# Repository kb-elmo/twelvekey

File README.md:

# Twelvekey

[![CC BY-NC-SA 4.0][cc-by-nc-sa-shield]][cc-by-nc-sa]

### Simple 12-key mechanical macropad

---

[STEP files for the case](case/)

[KiCAD PCB files](pcb/)

[Gerbers for PCB production](pcb/fab/twelvekey.zip)

[JLCPCB BOM](pcb/fab/twelvekey_bom_jlc.csv)

[JLCPCB CPL](pcb/fab/twelvekey_cpl_jlc.csv)

[Vial-QMK firmware](firmware/vial-qmk)

---

---

This work is licensed under a
[Creative Commons Attribution-NonCommercial-ShareAlike 4.0 International License][cc-by-nc-sa].

[![CC BY-NC-SA 4.0][cc-by-nc-sa-image]][cc-by-nc-sa]

[cc-by-nc-sa]: http://creativecommons.org/licenses/by-nc-sa/4.0/
[cc-by-nc-sa-image]: https://licensebuttons.net/l/by-nc-sa/4.0/88x31.png
[cc-by-nc-sa-shield]: https://img.shields.io/badge/License-CC%20BY--NC--SA%204.0-lightgrey.svg

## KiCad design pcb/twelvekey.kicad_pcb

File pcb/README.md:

# Twelvekey PCB

### Features

- In-switch LEDs
- Powered by an Atmega328p
- Basic ESD and overvoltage protection
- Centered USB type-C port for a detachable cable
- Fully programmable using [QMK](https://qmk.fm) and [Vial](https://get.vial.today)

---

### Preview

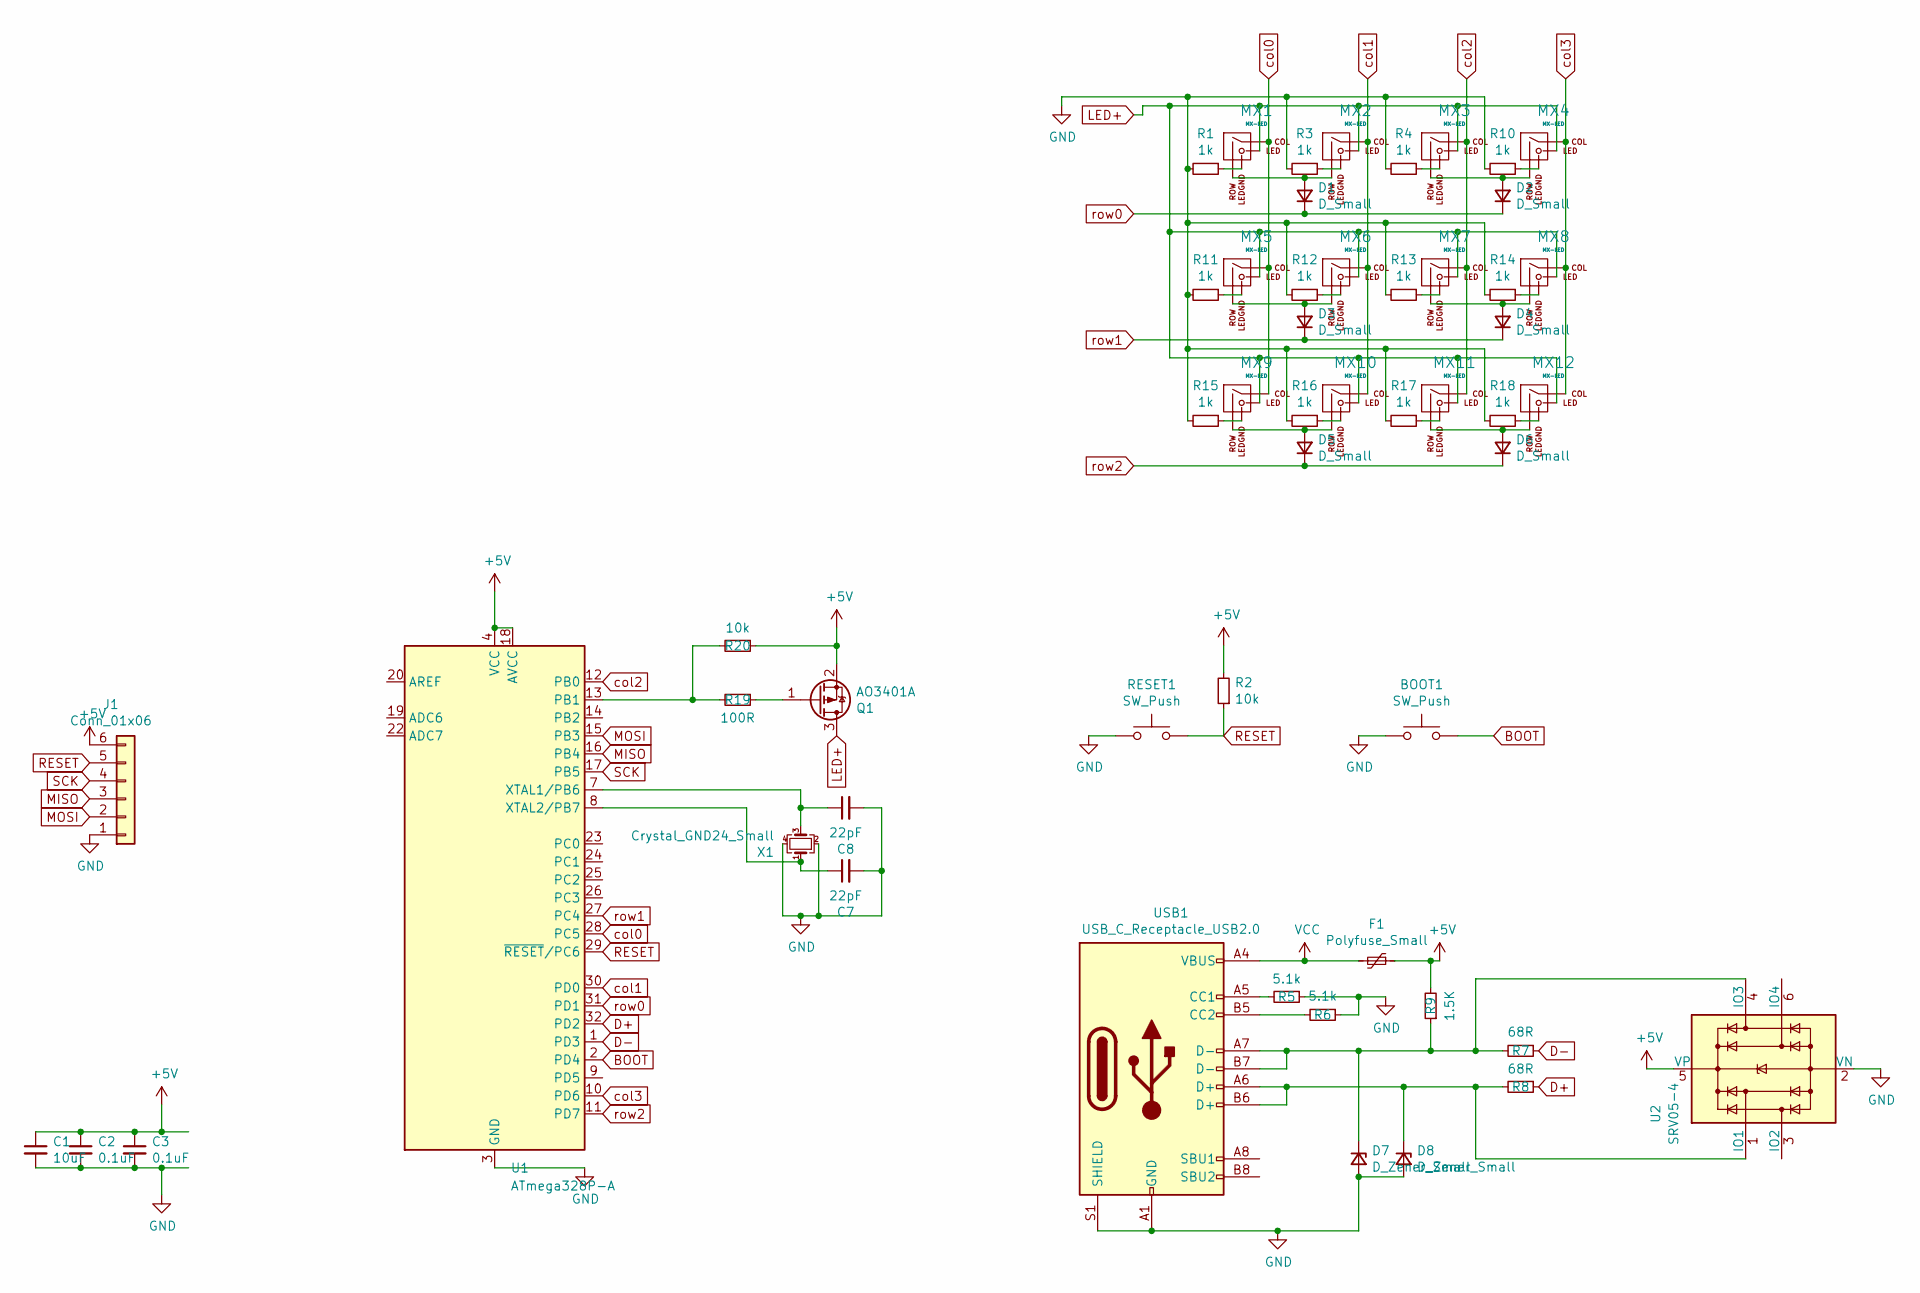
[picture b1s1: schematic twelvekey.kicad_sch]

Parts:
BOOT1: SW_Push; SKQG-1155865; LCSC C2762971
C1: 10uF; C_0805_2012Metric; LCSC C1713
C2, C3: 0.1uF; C_0805_2012Metric; LCSC C38141
C7, C8: 22pF; C_0805_2012Metric; LCSC C24658
D1, D2, D3, D4, D5, D6: D_Small; D_SOT-23_ANK; LCSC C408391
D7, D8: D_Zener_Small; D_SOD-123; LCSC C173412
F1: Polyfuse_Small; Fuse_1206_3216Metric; LCSC C151133
J1: Conn_01x06; PinHeader_1x06_P1.27mm_Vertical
MX1, MX2, MX3, MX4, MX5, MX6, MX7, MX8, MX9, MX10, MX11, MX12: MX-LED; MXOnly-1U
Q1: AO3401A; SOT-23; LCSC C15127
R1, R3, R4, R10, R11, R12, R13, R14, R15, R16, R17, R18: 1k; R_0805_2012Metric; LCSC C17513
R2, R20: 10k; R_0805_2012Metric; LCSC C17414
R5, R6: 5.1k; R_0805_2012Metric; LCSC C27834
R7, R8: 68R; R_0805_2012Metric; LCSC C17802
R9: 1.5K; R_0805_2012Metric; LCSC C4310
R19: 100R; R_0805_2012Metric; LCSC C17408
RESET1: SW_Push; SKQG-1155865; LCSC C2762971
U1: ATmega328P-A; TQFP-32_7x7mm_P0.8mm; LCSC C14877
U2: SRV05-4; SOT-23-6; LCSC C558418
USB1: USB_C_Receptacle_USB2.0; USB_C_Receptacle_HRO_TYPE-C-31-M-12; LCSC C165948
X1: Crystal_GND24_Small; Crystal_SMD_3225-4Pin_3.2x2.5mm; LCSC C13738

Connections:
+5V: C1.1, C2.1, C3.1, F1.1, J1.6, Q1.2 (S), R2.2, R9.2, R20.1, U1.4 (VCC), U1.6 (VCC), U1.18 (AVCC), U2.5 (VP)
BOOT: BOOT1.2, U1.2 (PD4); also elsewhere on the board
D+: R8.1, U1.32 (PD2)
D-: R7.1, U1.1 (PD3)
GND: BOOT1.1, C1.2, C2.2, C3.2, C7.2, C8.2, D7.2 (A), D8.2 (A), J1.1, R1.2, R3.2, R4.2, R5.1, R6.1, R10.2, R11.2, R12.2, R13.2, R14.2, R15.2, R16.2, R17.2, R18.2, RESET1.1, U1.3 (GND), U1.5 (GND), U1.21 (GND), U2.2 (VN), USB1.A1 (GND), USB1.A12 (GND), USB1.B1 (GND), USB1.B12 (GND), USB1.S1 (SHIELD), X1.2, X1.4; also elsewhere on the board
LED+: MX1.3 (LED), MX2.3 (LED), MX3.3 (LED), MX4.3 (LED), MX5.3 (LED), MX6.3 (LED), MX7.3 (LED), MX8.3 (LED), MX9.3 (LED), MX10.3 (LED), MX11.3 (LED), MX12.3 (LED), Q1.3 (D)
MISO: J1.3, U1.16 (PB4)
MOSI: J1.2, U1.15 (PB3)
unnamed: D1.2 (A), MX1.2 (ROW), MX2.2 (ROW)
unnamed: D2.2 (A), MX3.2 (ROW), MX4.2 (ROW)
unnamed: D3.2 (A), MX5.2 (ROW), MX6.2 (ROW)
unnamed: D4.2 (A), MX7.2 (ROW), MX8.2 (ROW)
unnamed: D5.2 (A), MX9.2 (ROW), MX10.2 (ROW)
unnamed: D6.2 (A), MX11.2 (ROW), MX12.2 (ROW)
unnamed: D7.1 (K), R7.2, R9.1, U2.4 (IO3), USB1.A7 (D-), USB1.B7 (D-)
unnamed: D8.1 (K), R8.2, U2.1 (IO1), USB1.A6 (D+), USB1.B6 (D+)
unnamed: MX1.4 (LEDGND), R1.1
unnamed: MX2.4 (LEDGND), R3.1
unnamed: MX3.4 (LEDGND), R4.1
unnamed: MX4.4 (LEDGND), R10.1
unnamed: MX5.4 (LEDGND), R11.1
unnamed: MX6.4 (LEDGND), R12.1
unnamed: MX7.4 (LEDGND), R13.1
unnamed: MX8.4 (LEDGND), R14.1
unnamed: MX9.4 (LEDGND), R15.1
unnamed: MX10.4 (LEDGND), R16.1
unnamed: MX11.4 (LEDGND), R17.1
unnamed: MX12.4 (LEDGND), R18.1
unnamed: Q1.1 (G), R19.1
unnamed: R19.2, R20.2, U1.13 (PB1)
unnamed: C8.1, U1.7 (XTAL1/PB6), X1.3
unnamed: C7.1, U1.8 (XTAL2/PB7), X1.1
unnamed: R5.2, USB1.A5 (CC1)
unnamed: R6.2, USB1.B5 (CC2)
RESET: J1.5, R2.1, RESET1.2, U1.29 (~RESET/PC6); also elsewhere on the board
SCK: J1.4, U1.17 (PB5)
VCC: F1.2, USB1.A4 (VBUS), USB1.A9 (VBUS), USB1.B4 (VBUS), USB1.B9 (VBUS)
col0: MX1.1 (COL), MX5.1 (COL), MX9.1 (COL), U1.28 (PC5)
col1: MX2.1 (COL), MX6.1 (COL), MX10.1 (COL), U1.30 (PD0)
col2: MX3.1 (COL), MX7.1 (COL), MX11.1 (COL), U1.12 (PB0)
col3: MX4.1 (COL), MX8.1 (COL), MX12.1 (COL), U1.10 (PD6)
row0: D1.1 (K), D2.1 (K), U1.31 (PD1)
row1: D3.1 (K), D4.1 (K), U1.27 (PC4)
row2: D5.1 (K), D6.1 (K), U1.11 (PD7)

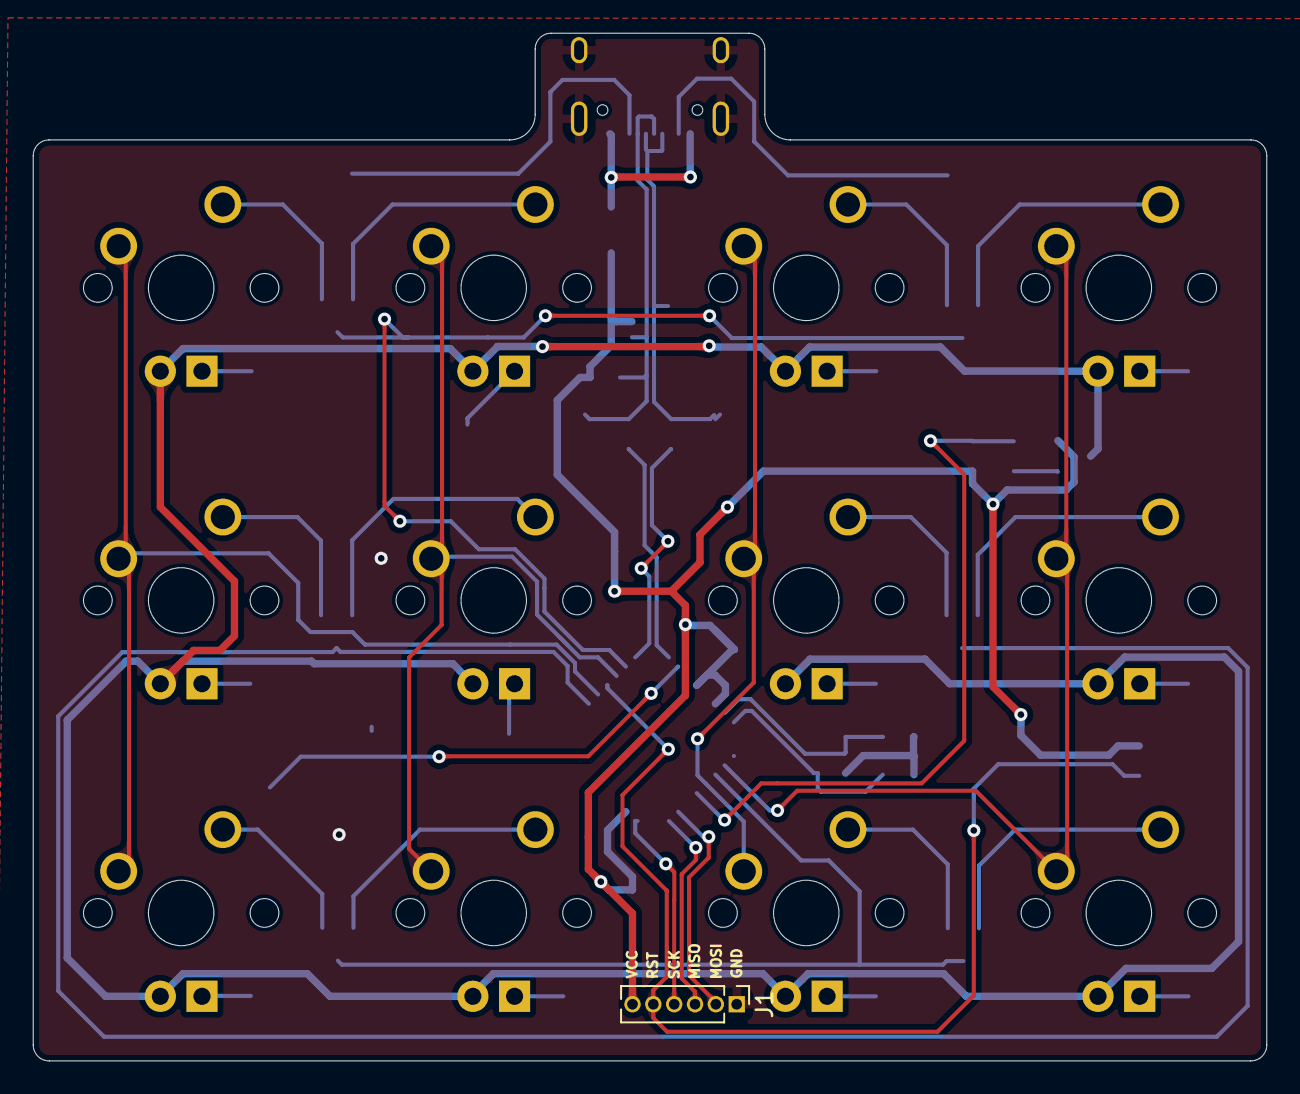
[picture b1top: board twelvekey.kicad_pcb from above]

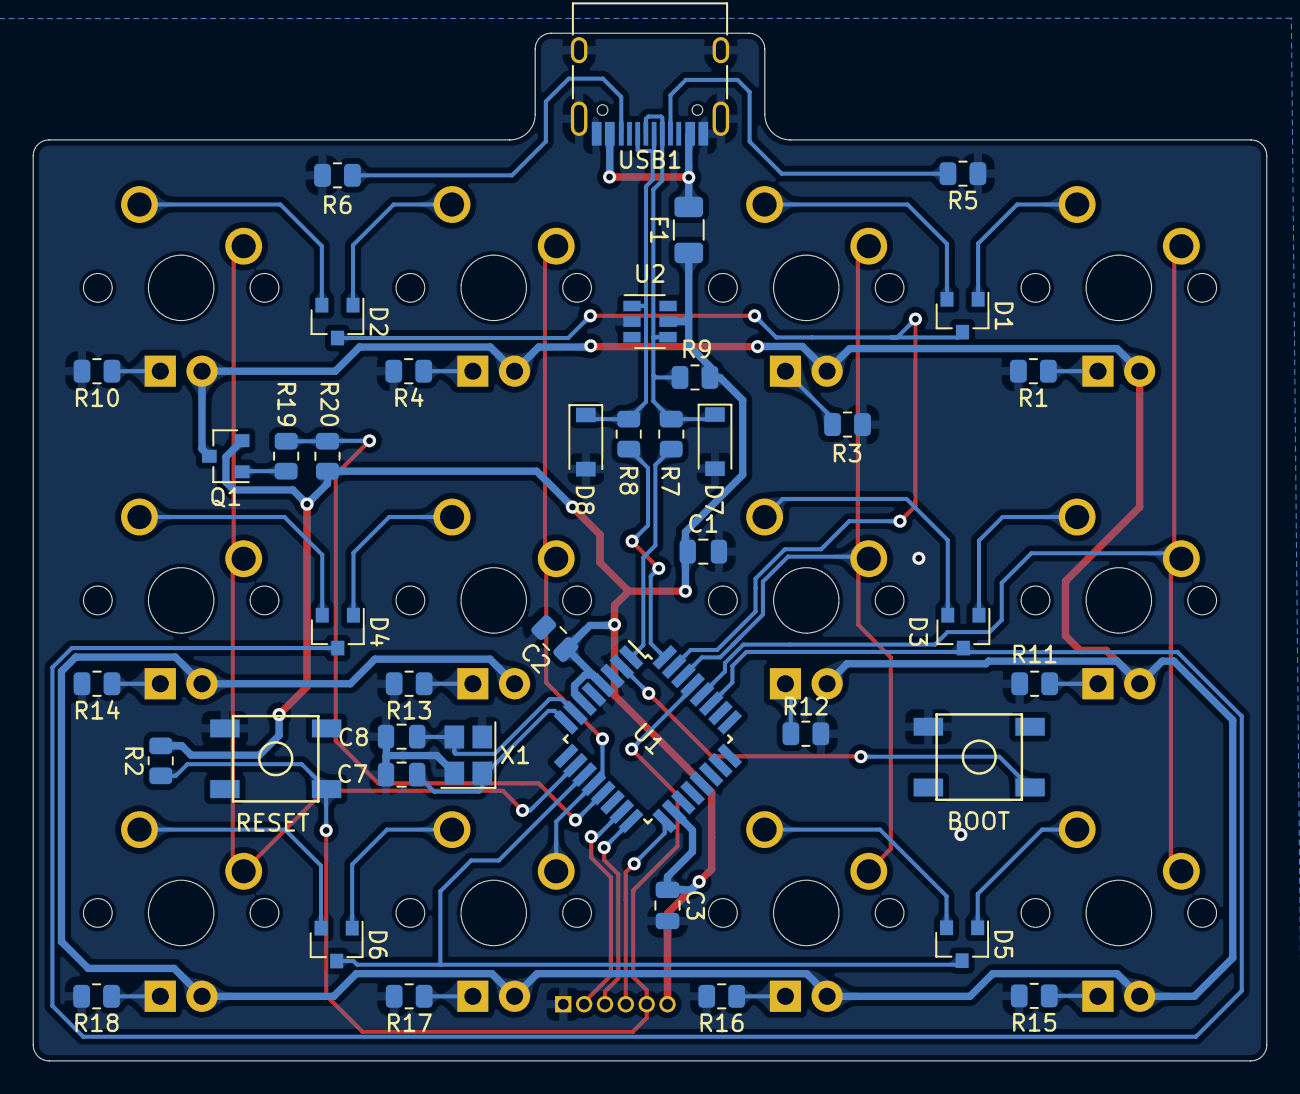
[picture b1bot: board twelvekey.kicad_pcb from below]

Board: 2 copper layers, 75.2 x 62.6 mm, 54 parts (41 on the bottom side), 44 nets.

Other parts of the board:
BOOT: SW_Push; SKQG-1155865
RESET: SW_Push; SKQG-1155865

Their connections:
BOOT: BOOT.2; also elsewhere on the board
GND: BOOT.1, RESET.1; also elsewhere on the board
RESET: RESET.2; also elsewhere on the board

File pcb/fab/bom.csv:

Designator,Footprint,Quantity,Value,LCSC Part #
"BOOT, RESET",SKQG-1155865,2,SW_Push,C2762971
C1,0805,1,10uF,C1713
"C2, C3",0805,2,0.1uF,C38141
"C7, C8",0805,2,22pF,C24658
"D1, D2, D3, D4, D5, D6",D_SOT-23_ANK,6,D_Small,C408391
"D7, D8",D_SOD-123,2,D_Zener_Small,C173412
F1,1206,1,Polyfuse_Small,C151133
J1,PinHeader_1x06_P1.27mm_Vertical,1,Conn_01x06,
"MX1, MX10, MX11, MX12, MX2, MX3, MX4, MX5, MX6, MX7, MX8, MX9",MXOnly-1U,12,MX-LED,
Q1,SOT-23,1,AO3401A,C15127
"R1, R10, R11, R12, R13, R14, R15, R16, R17, R18, R3, R4",0805,12,1k,C17513
R19,0805,1,100R,C17408
"R2, R20",0805,2,10k,C17414
"R5, R6",0805,2,5.1k,C27834
"R7, R8",0805,2,68R,C17802
R9,0805,1,1.5K,C4310
U1,TQFP-32_7x7mm_P0.8mm,1,ATmega328P-A,C14877
U2,SOT-23-6,1,SRV05-4,C558418
USB1,USB_C_Receptacle_HRO_TYPE-C-31-M-12,1,USB_C_Receptacle_USB2.0,C165948
X1,Crystal_SMD_3225-4Pin_3.2x2.5mm,1,Crystal_GND24_Small,C13738

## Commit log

2021-01-04 add PCB
2021-01-04 add readme and fabrication files
2021-01-04 add PCB to STEP
2021-01-04 update pcb images
2021-01-04 change images
2021-01-04 rename
2021-01-04 Create LICENSE
2021-01-05 change readme images
2021-01-17 updated PCB to support per-key LEDs
2021-01-17 added a logo
2021-02-17 fix backlight
2021-03-18 update images
2021-04-05 update and added 3d print files
2021-09-30 new version update
2021-09-30 add firmware
2021-10-02 add gerbers
2021-10-03 add bootloader
2024-02-25 fix bootloader firmware
2024-02-25 update vial-qmk firmware
2024-02-25 fix readme
